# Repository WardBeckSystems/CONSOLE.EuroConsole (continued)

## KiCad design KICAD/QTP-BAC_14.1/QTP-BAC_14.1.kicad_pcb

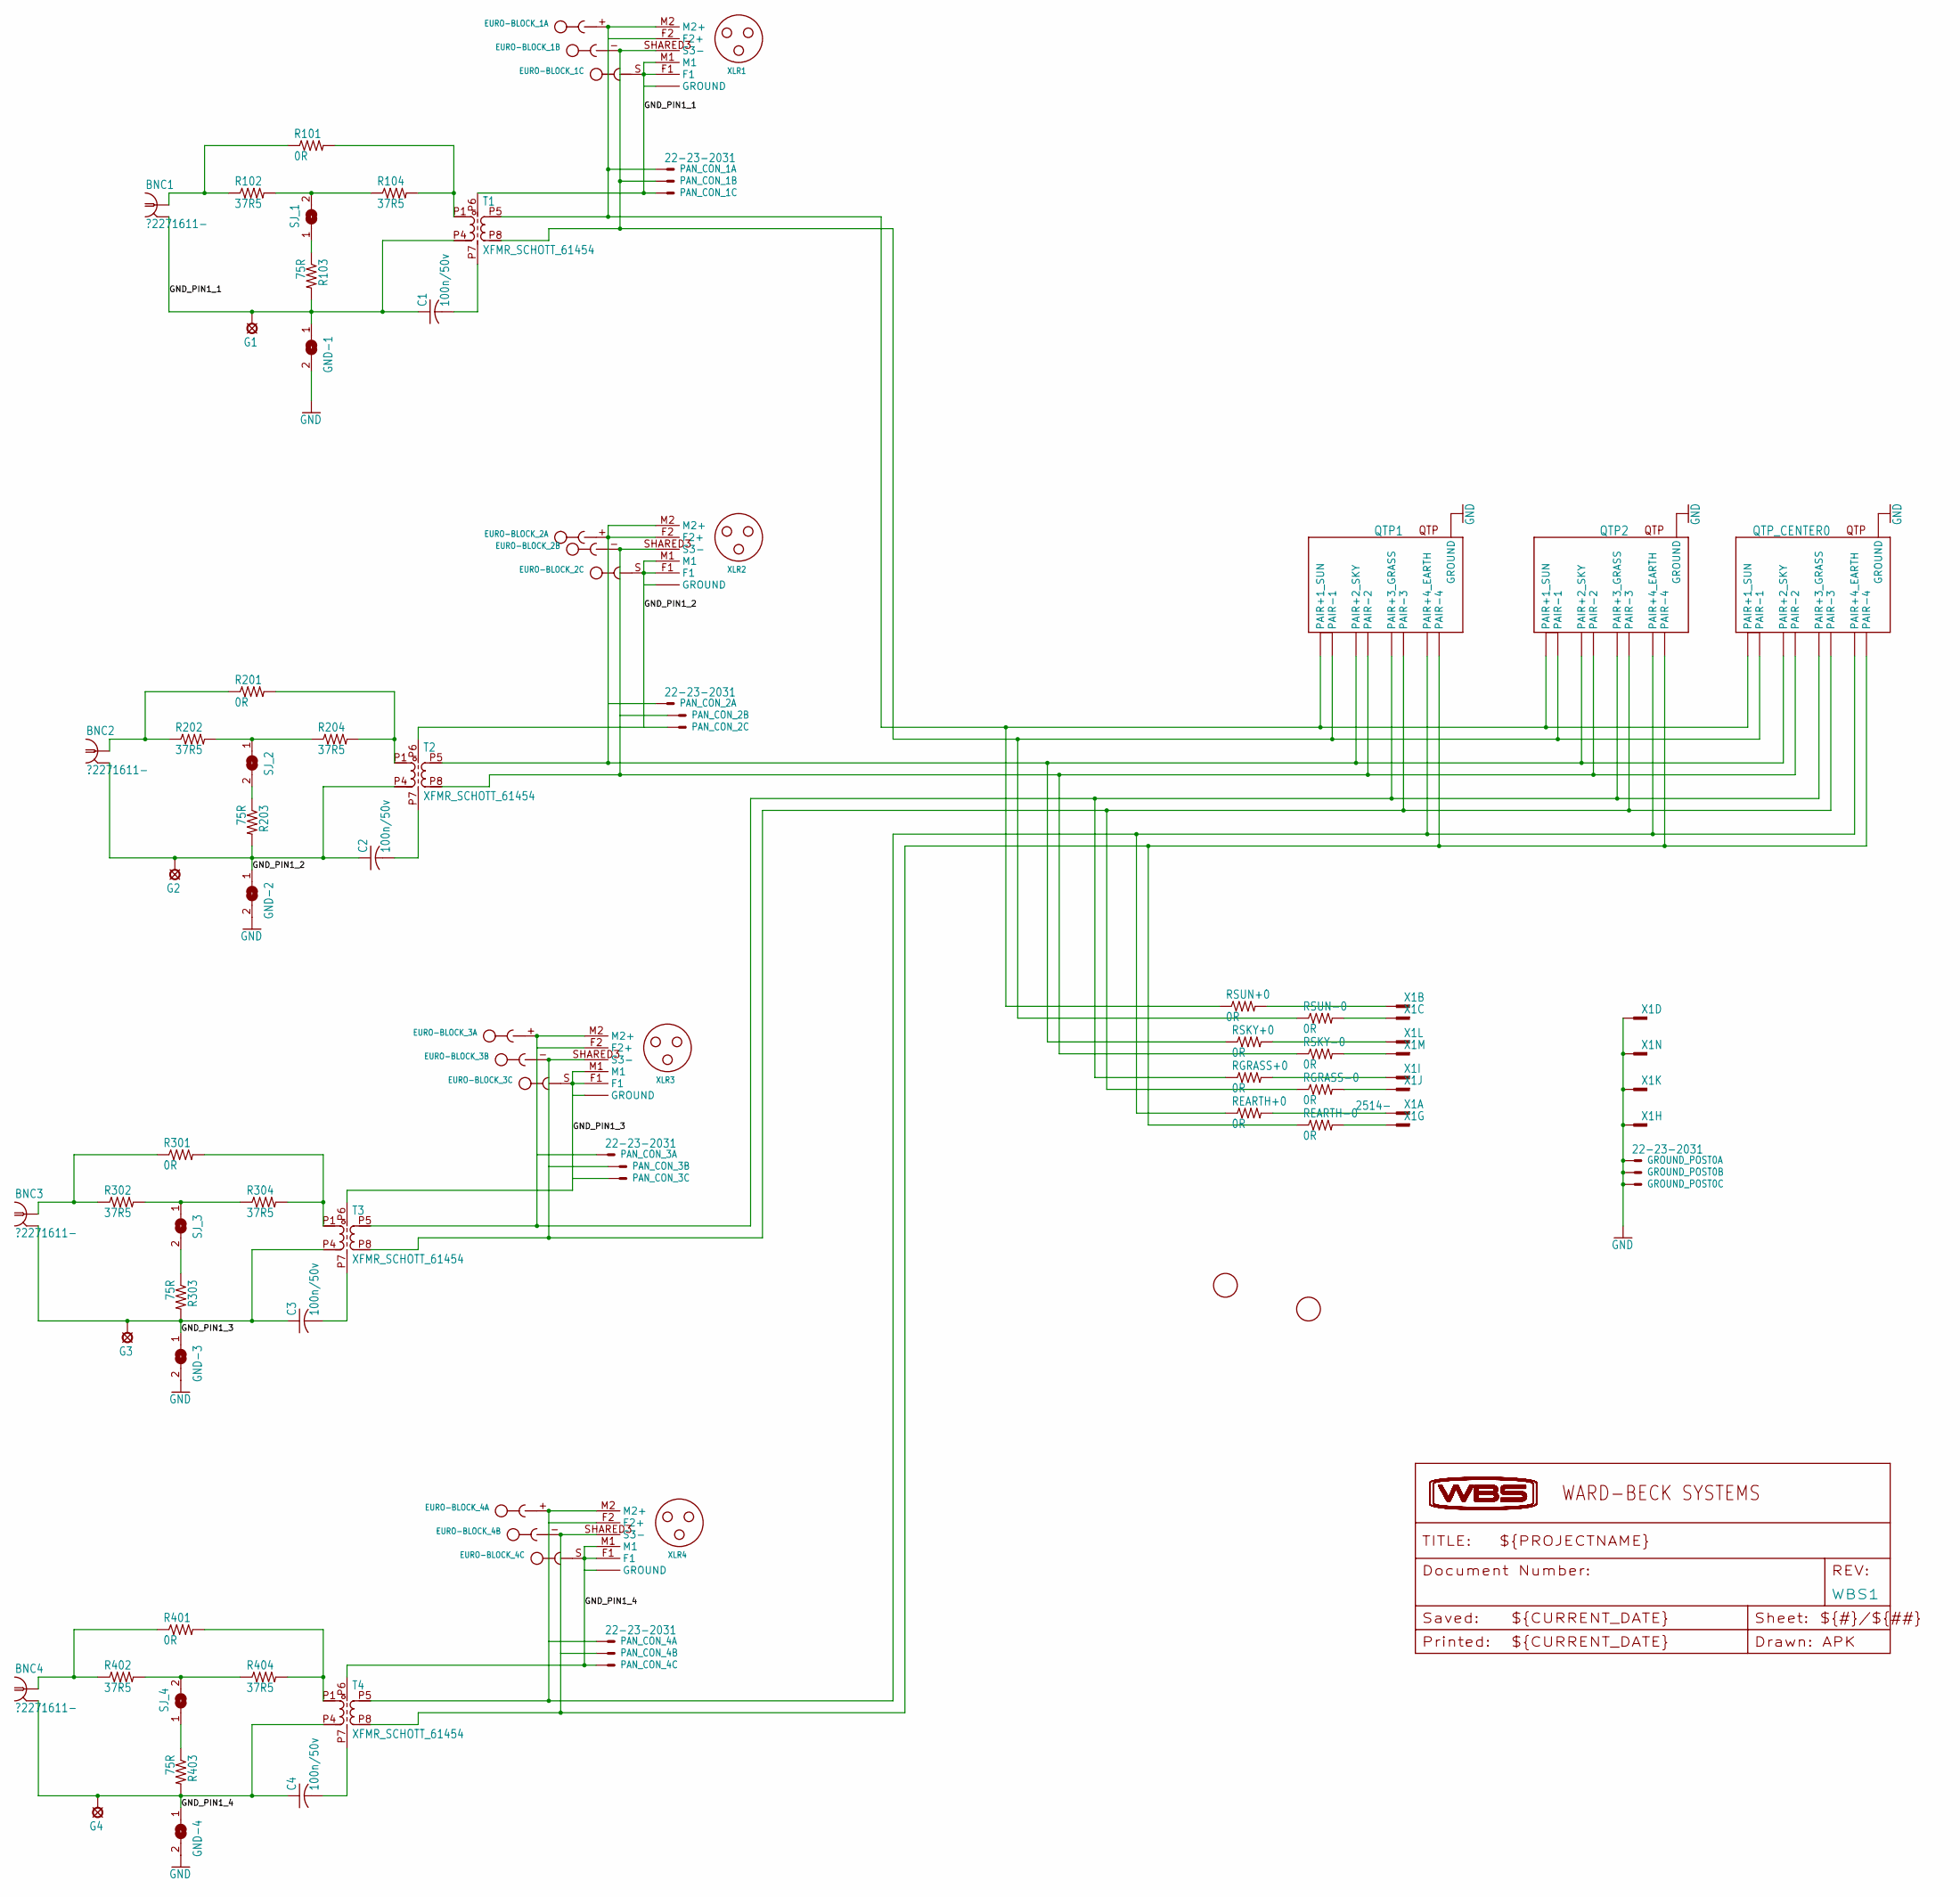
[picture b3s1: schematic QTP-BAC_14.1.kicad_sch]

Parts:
BNC1, BNC2, BNC3, BNC4: ?2271611-; AMP_227161
C1, C2, C3, C4: 100n/50v; C0805
EURO-BLOCK_1, EURO-BLOCK_2, EURO-BLOCK_3, EURO-BLOCK_4: CON-PHOENIX_RIGHT_ANGLE_3.81; CON-PHOENIX_MC1.5_3-G-3.81
G1, G2, G3, G4: LSP10
GND-1, GND-2, GND-3, GND-4: SJ
GROUND_POST0: 22-23-2031
PAN_CON_1, PAN_CON_2, PAN_CON_3, PAN_CON_4: 22-23-2031
QTP1, QTP2: CON-QTP; ASSMAN-RJ45
QTP_CENTER0: CON-QTP; ASSMAN-RJ45
R101, R201, R301, R401: 0R; R0805W
R102, R104, R202, R204, R302, R304, R402, R404: 37R5; R0805W
R103, R203, R303, R403: 75R; R0805W
REARTH+0: 0R; R0805W
REARTH-0: 0R; R0805W
RGRASS+0: 0R; R0805W
RGRASS-0: 0R; R0805W
RSKY+0: 0R; R0805W
RSKY-0: 0R; R0805W
RSUN+0: 0R; R0805W
RSUN-0: 0R; R0805W
SJ_1, SJ_2, SJ_3, SJ_4: SJ
T1, T2, T3, T4: XFMR_SCHOTT_61454; SCHOTT_61454
U$1, U$2: FIDUCIAL; FIDUCIAL_1MM
WBS1: WBS-DOCUMENT_INFO_FRAME; WBS-FRAME_PCB
X1: 2514-; PAK100_2500-14
XLR1, XLR2, XLR3, XLR4: CON-XLR-NEUTRIK_A_BISEXUAL; CON_NEUTRIK_A_BISEXUAL_H

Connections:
CH1-1: EURO-BLOCK_1.-, PAN_CON_1.2, QTP1.P1- (PAIR-1), QTP2.P1- (PAIR-1), QTP_CENTER0.P1- (PAIR-1), RSUN-0.1, T1.P8, XLR1.SHARED3 (S3-)
CH2+1: EURO-BLOCK_2.+, PAN_CON_2.1, QTP1.P2+ (PAIR+2_SKY), QTP2.P2+ (PAIR+2_SKY), QTP_CENTER0.P2+ (PAIR+2_SKY), RSKY+0.1, T2.P5, XLR2.F2 (F2+), XLR2.M2 (M2+)
CH2-1: EURO-BLOCK_2.-, PAN_CON_2.2, QTP1.P2- (PAIR-2), QTP2.P2- (PAIR-2), QTP_CENTER0.P2- (PAIR-2), RSKY-0.1, T2.P8, XLR2.SHARED3 (S3-)
CH3+1: EURO-BLOCK_3.+, PAN_CON_3.1, QTP1.P3+ (PAIR+3_GRASS), QTP2.P3+ (PAIR+3_GRASS), QTP_CENTER0.P3+ (PAIR+3_GRASS), RGRASS+0.1, T3.P5, XLR3.F2 (F2+), XLR3.M2 (M2+)
CH3-1: EURO-BLOCK_3.-, PAN_CON_3.2, QTP1.P3- (PAIR-3), QTP2.P3- (PAIR-3), QTP_CENTER0.P3- (PAIR-3), RGRASS-0.1, T3.P8, XLR3.SHARED3 (S3-)
CH4+1: EURO-BLOCK_4.+, PAN_CON_4.1, QTP1.P4+ (PAIR+4_EARTH), QTP2.P4+ (PAIR+4_EARTH), QTP_CENTER0.P4+ (PAIR+4_EARTH), REARTH+0.1, T4.P5, XLR4.F2 (F2+), XLR4.M2 (M2+)
CH4-1: EURO-BLOCK_4.-, PAN_CON_4.2, QTP1.P4- (PAIR-4), QTP2.P4- (PAIR-4), QTP_CENTER0.P4- (PAIR-4), REARTH-0.1, T4.P8, XLR4.SHARED3 (S3-)
GND: GND-1.2, GND-2.2, GND-3.2, GND-4.2, GROUND_POST0.1, GROUND_POST0.2, GROUND_POST0.3, QTP1.P$9 (GROUND), QTP1.P$10 (GROUND), QTP1.P$11 (GROUND), QTP1.P$12 (GROUND), QTP2.P$9 (GROUND), QTP2.P$10 (GROUND), QTP2.P$11 (GROUND), QTP2.P$12 (GROUND), QTP_CENTER0.P$9 (GROUND), QTP_CENTER0.P$10 (GROUND), QTP_CENTER0.P$11 (GROUND), QTP_CENTER0.P$12 (GROUND), X1.3, X1.6, X1.9, X1.12
GND_PIN1_2: BNC2.2, C2.1, EURO-BLOCK_2.S, G2.MP, GND-2.1, PAN_CON_2.3, R203.2, T2.P4, T2.P6, XLR2.CHASSIS (GROUND), XLR2.F1, XLR2.GROUND, XLR2.M1
GND_PIN1_3: BNC3.2, C3.1, EURO-BLOCK_3.S, G3.MP, GND-3.1, PAN_CON_3.3, R303.2, T3.P4, T3.P6, XLR3.CHASSIS (GROUND), XLR3.F1, XLR3.GROUND, XLR3.M1
GND_PIN1_4: BNC4.2, C4.1, EURO-BLOCK_4.S, G4.MP, GND-4.1, PAN_CON_4.3, R403.2, T4.P4, T4.P6, XLR4.CHASSIS (GROUND), XLR4.F1, XLR4.GROUND, XLR4.M1
unnamed: R102.2, R104.1, SJ_1.2
unnamed: C1.2, T1.P7
unnamed: R101.2, R104.2, T1.P1
unnamed: R103.1, SJ_1.1
unnamed: BNC1.1, R101.1, R102.1
unnamed: R203.1, SJ_2.2
unnamed: R303.1, SJ_3.2
unnamed: R201.2, R204.2, T2.P1
unnamed: R202.2, R204.1, SJ_2.1
unnamed: BNC2.1, R201.1, R202.1
unnamed: C2.2, T2.P7
unnamed: R403.1, SJ_4.1
unnamed: R301.2, R304.2, T3.P1
unnamed: R302.2, R304.1, SJ_3.1
unnamed: BNC3.1, R301.1, R302.1
unnamed: C3.2, T3.P7
unnamed: R401.2, R404.2, T4.P1
unnamed: R402.2, R404.1, SJ_4.2
unnamed: BNC4.1, R401.1, R402.1
unnamed: C4.2, T4.P7
unnamed: REARTH-0.2, X1.2
unnamed: REARTH+0.2, X1.1
unnamed: RGRASS-0.2, X1.5
unnamed: RSUN+0.2, X1.10
unnamed: RGRASS+0.2, X1.4
unnamed: RSKY-0.2, X1.8
unnamed: RSKY+0.2, X1.7
unnamed: RSUN-0.2, X1.11

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
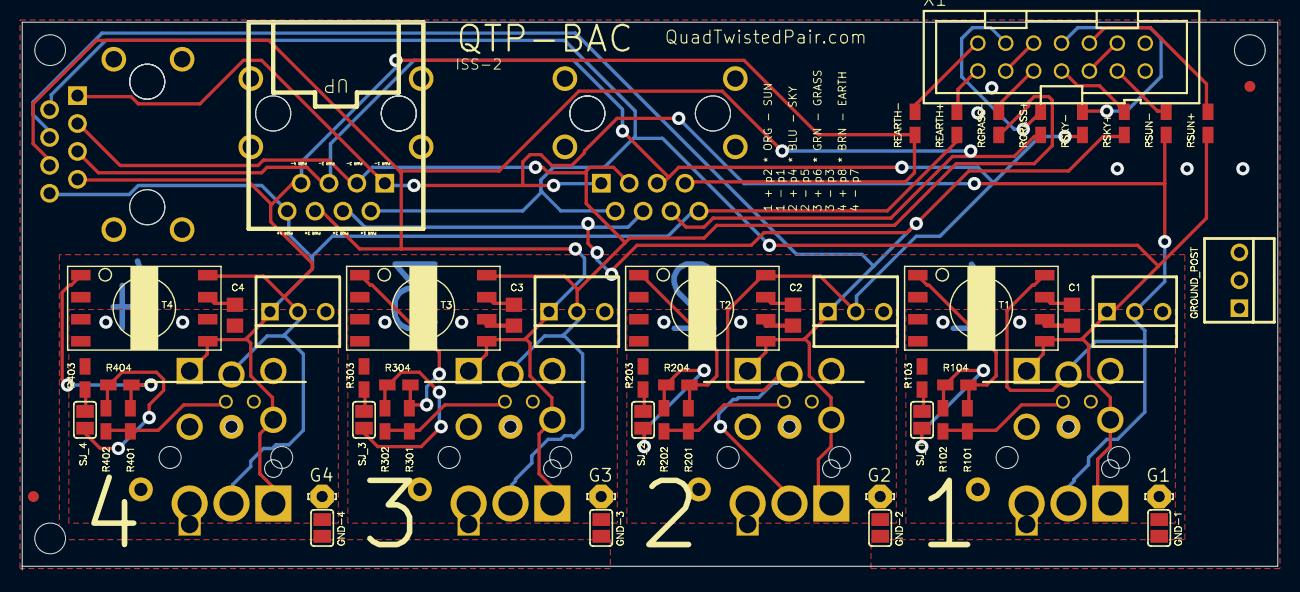
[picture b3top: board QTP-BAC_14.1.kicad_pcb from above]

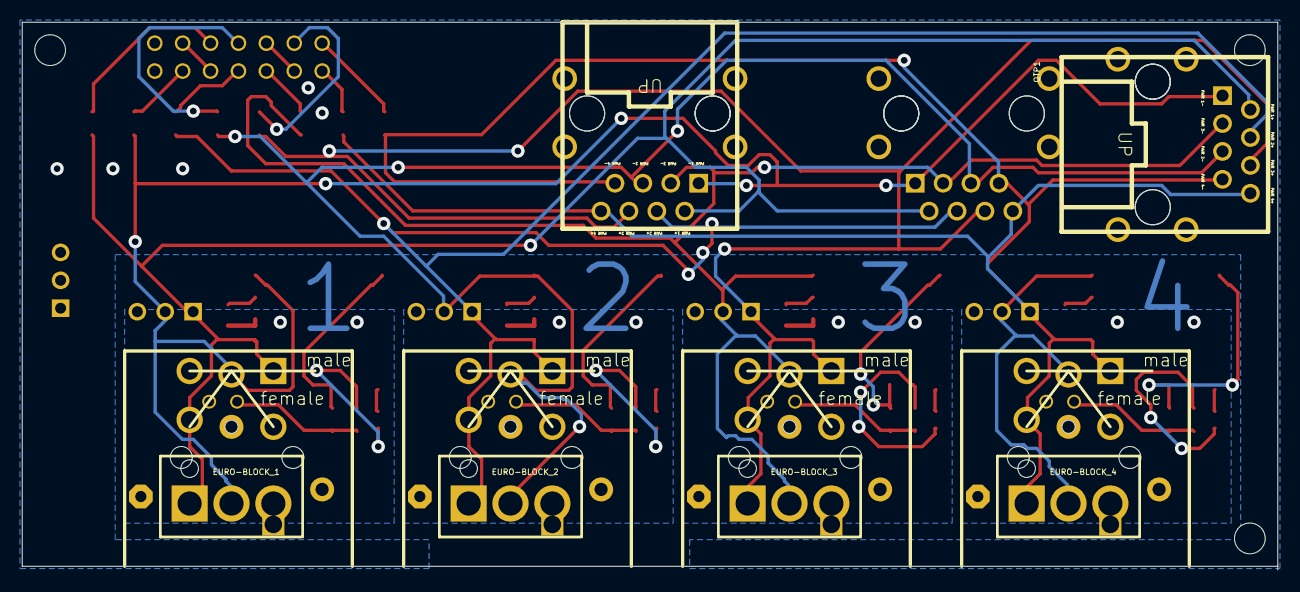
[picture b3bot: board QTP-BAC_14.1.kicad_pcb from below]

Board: 2 copper layers, 114.3 x 49.5 mm, 112 parts (6 on the bottom side), 41 nets.

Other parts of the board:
U$4: C1-4-150731-094535
U$5: C2-5-150731-094535
U$6: C3-6-150731-094535
U$7: C4-7-150731-094535
U$9: GND_1-8-150731-094535
U$10: GND_2-9-150731-094535
U$11: GND_3-10-150731-094535
U$12: GND_4-11-150731-094535
U$13: GROUND_P-12-150731-094535
U$18: R101-17-150731-094535
U$19: R102-18-150731-094535
U$20: R103-19-150731-094535
U$21: R104-20-150731-094535
U$22: R201-21-150731-094535
U$23: R202-22-150731-094535
U$24: R203-23-150731-094535
U$25: R204-24-150731-094535
U$26: R301-25-150731-094535
U$27: R302-26-150731-094535
U$28: R303-27-150731-094535
U$29: R304-28-150731-094535
U$30: R401-29-150731-094535
U$31: R402-30-150731-094535
U$32: R403-31-150731-094535
U$33: R404-32-150731-094535
U$34: REARTH_-33-150731-094535
U$35: REARTH_-34-150731-094535
U$36: RGRASS_-35-150731-094535
U$37: RGRASS_-36-150731-094535
U$38: RSKY_-37-150731-094535
U$39: RSKY_-38-150731-094535
U$40: RSUN_-39-150731-094535
U$41: RSUN_-40-150731-094535
U$42: SJ_1-41-150731-094535
U$43: SJ_2-42-150731-094536
U$44: SJ_3-43-150731-094536
U$45: SJ_4-44-150731-094536
U$46: GND_PIN1_1; T1-45-150731-094536
U$47: GND_PIN1_2; T2-46-150731-094536
U$48: gnd; T3-47-150731-094536
U$49: gnd; T4-48-150731-094536
UNK_HOLE_0: dummyfp0
UNK_HOLE_1: dummyfp1
UNK_HOLE_2: dummyfp2

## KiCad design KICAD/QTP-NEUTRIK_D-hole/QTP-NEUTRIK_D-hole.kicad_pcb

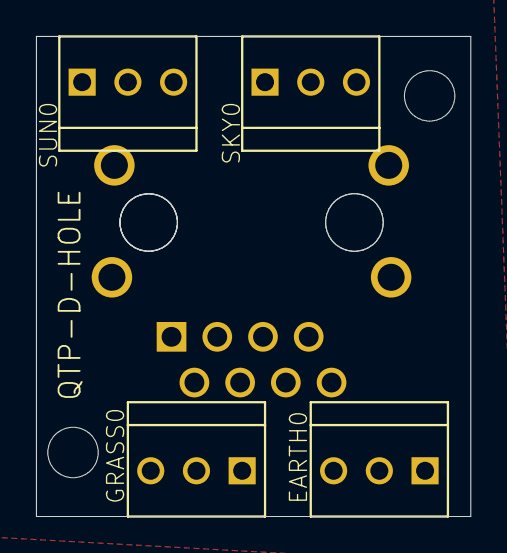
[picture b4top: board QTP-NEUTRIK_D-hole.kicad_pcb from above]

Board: 2 copper layers, 24.1 x 26.7 mm, 7 parts (1 on the bottom side), 9 nets, no tracks yet.

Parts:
EARTH0: CON-WBS-LOCKING-0.1-3
GRASS0: CON-WBS-LOCKING-0.1-3
SKY0: CON-WBS-LOCKING-0.1-3
SUN0: CON-WBS-LOCKING-0.1-3
U$1: CON-QTP_VERT; ASSMAN-RJ45_VERT
UNK_HOLE_0: dummyfp0
UNK_HOLE_1: dummyfp1

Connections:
GND: EARTH0.P$3, GRASS0.P$3, SKY0.P$3, SUN0.P$3, U$1.P$9, U$1.P$10, U$1.P$11, U$1.P$12
unnamed: SUN0.P$1, U$1.P$2
unnamed: SUN0.P$2, U$1.P$1
unnamed: SKY0.P$1, U$1.P$4
unnamed: GRASS0.P$1, U$1.P$6
unnamed: GRASS0.P$2, U$1.P$3
unnamed: EARTH0.P$1, U$1.P$8
unnamed: EARTH0.P$2, U$1.P$7
SUN_N: SKY0.P$2, U$1.P$5

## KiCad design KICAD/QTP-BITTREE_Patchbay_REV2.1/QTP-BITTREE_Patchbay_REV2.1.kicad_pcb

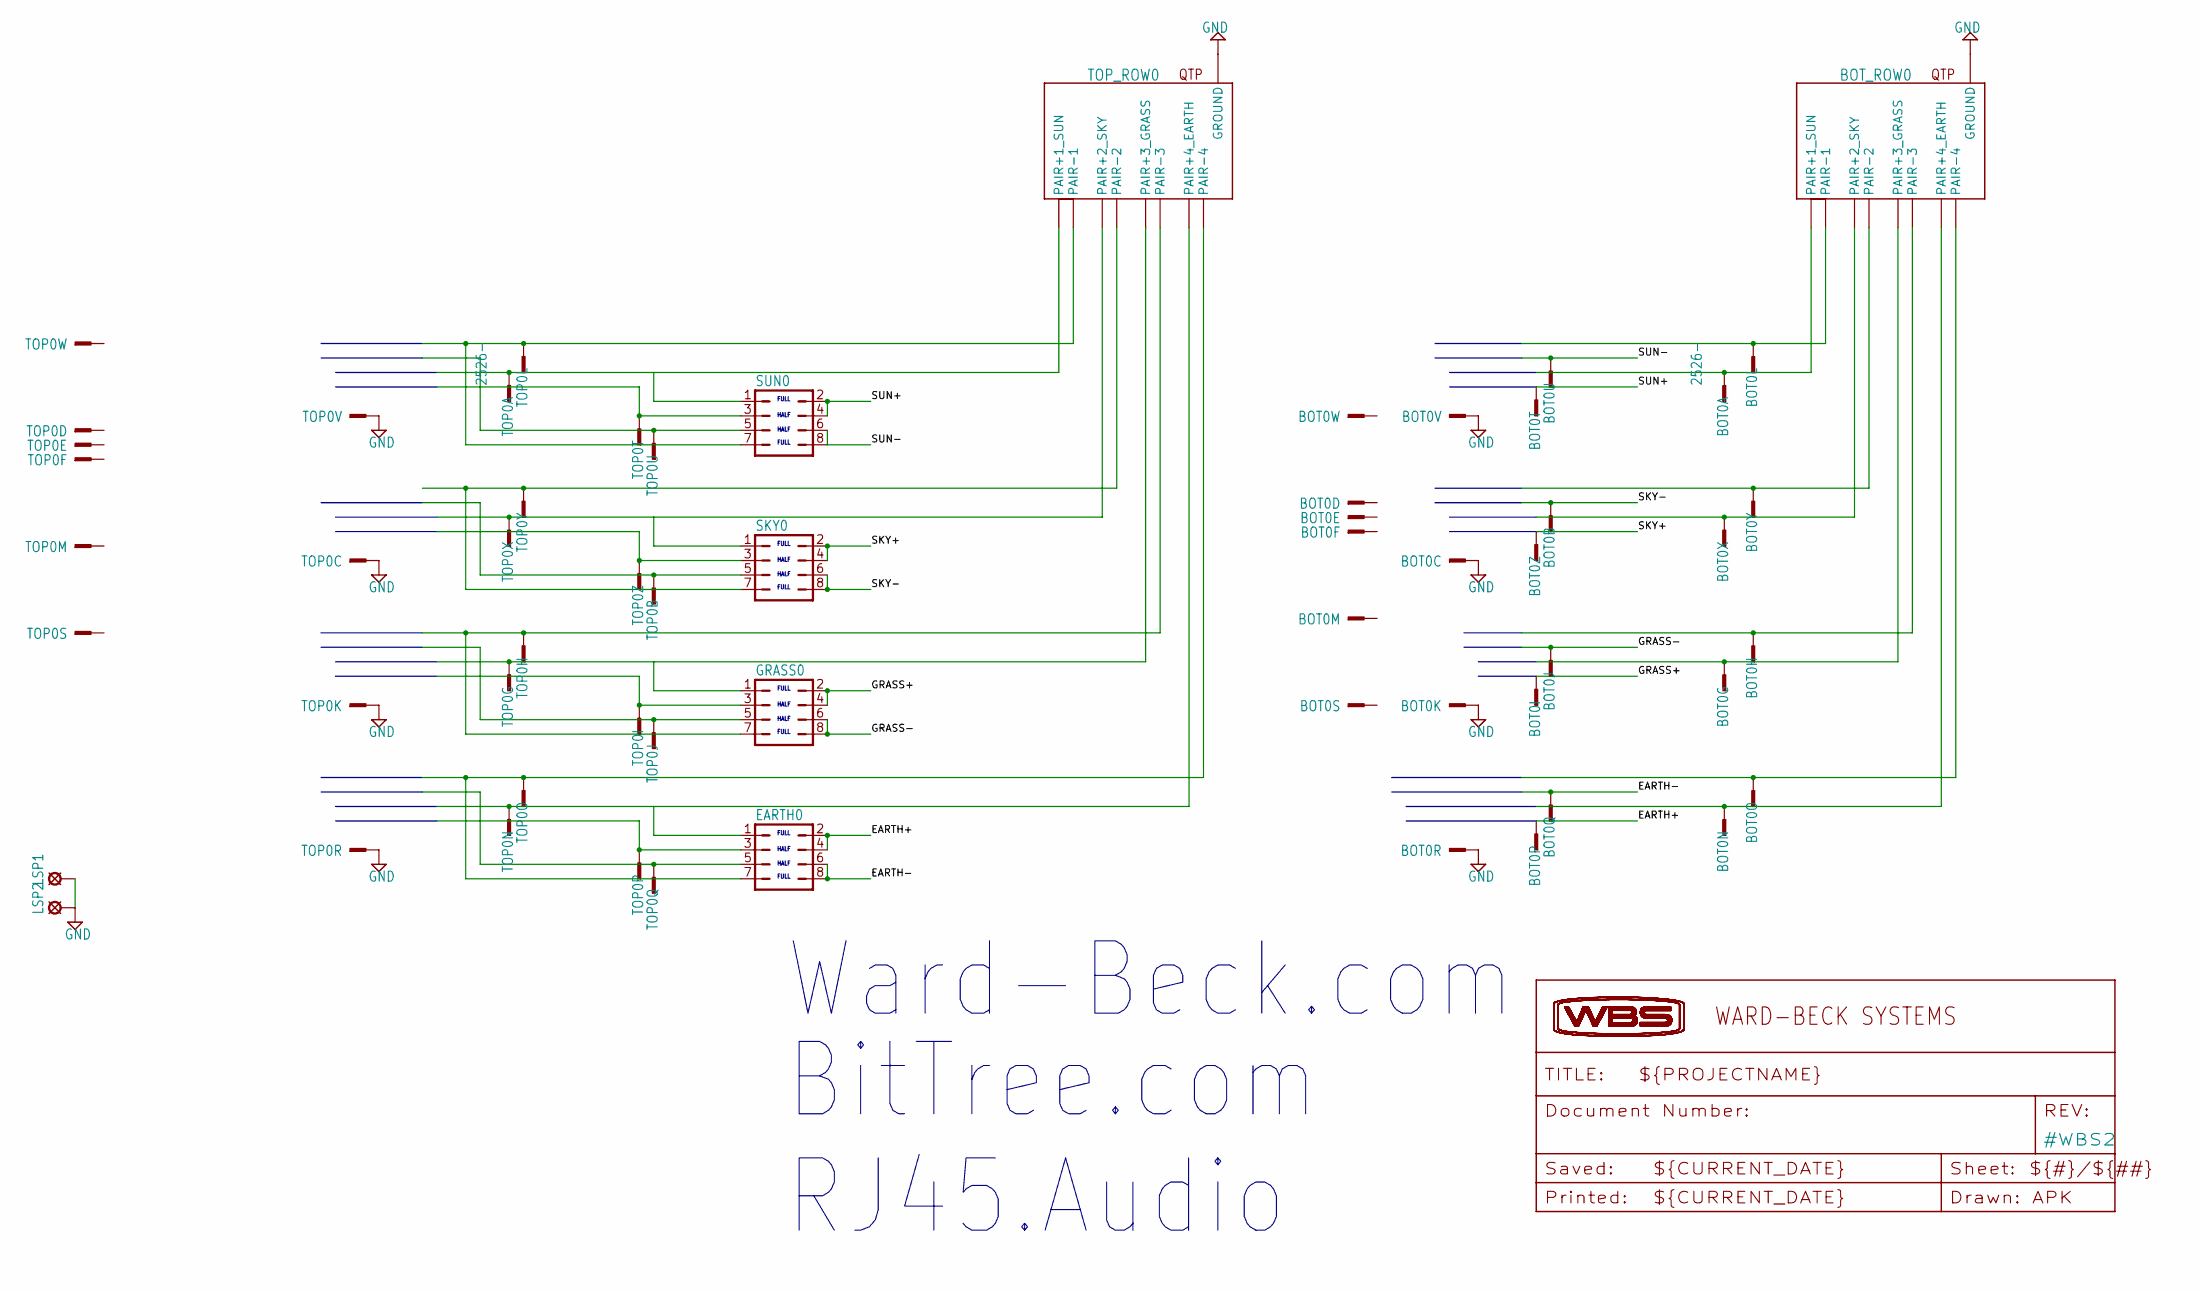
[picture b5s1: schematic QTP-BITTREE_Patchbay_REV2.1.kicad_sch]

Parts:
BOT0: 2526-; PAK100_2500-26
BOT_ROW0: CON-QTP_VERT; ASSMAN-RJ45_VERT
EARTH0: JP4Q
GRASS0: JP4Q
LSP1, LSP2: LSP13
SKY0: JP4Q
SUN0: JP4Q
TOP0: 2526-; PAK100_2500-26
TOP_ROW0: CON-QTP_VERT; ASSMAN-RJ45_VERT

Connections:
EARTH+: BOT0.23, EARTH0.2, EARTH0.4
EARTH-: BOT0.24, EARTH0.6, EARTH0.8
GND: BOT0.5, BOT0.11, BOT0.19, BOT0.25, BOT_ROW0.P$9 (GROUND), BOT_ROW0.P$10 (GROUND), BOT_ROW0.P$11 (GROUND), BOT_ROW0.P$12 (GROUND), LSP1.MP, LSP2.MP, TOP0.5, TOP0.11, TOP0.19, TOP0.25, TOP_ROW0.P$9 (GROUND), TOP_ROW0.P$10 (GROUND), TOP_ROW0.P$11 (GROUND), TOP_ROW0.P$12 (GROUND)
GRASS+: BOT0.17, GRASS0.2, GRASS0.4
GRASS-: BOT0.18, GRASS0.6, GRASS0.8
unnamed: SUN0.7, TOP0.2, TOP_ROW0.P$1 (PAIR-1)
unnamed: SKY0.1, TOP0.7, TOP_ROW0.P$4 (PAIR+2_SKY)
unnamed: BOT0.1, BOT_ROW0.P$2 (PAIR+1_SUN)
unnamed: GRASS0.1, TOP0.15, TOP_ROW0.P$6 (PAIR+3_GRASS)
unnamed: BOT0.2, BOT_ROW0.P$1 (PAIR-1)
unnamed: EARTH0.1, TOP0.21, TOP_ROW0.P$8 (PAIR+4_EARTH)
unnamed: SUN0.3, TOP0.3
unnamed: SUN0.5, TOP0.4
unnamed: BOT0.7, BOT_ROW0.P$4 (PAIR+2_SKY)
unnamed: SKY0.7, TOP0.8, TOP_ROW0.P$5 (PAIR-2)
unnamed: SKY0.3, TOP0.9
unnamed: SKY0.5, TOP0.10
unnamed: BOT0.15, BOT_ROW0.P$6 (PAIR+3_GRASS)
unnamed: GRASS0.7, TOP0.16, TOP_ROW0.P$3 (PAIR-3)
unnamed: GRASS0.3, TOP0.17
unnamed: GRASS0.5, TOP0.18
unnamed: BOT0.21, BOT_ROW0.P$8 (PAIR+4_EARTH)
unnamed: EARTH0.7, TOP0.22, TOP_ROW0.P$7 (PAIR-4)
unnamed: EARTH0.3, TOP0.23
unnamed: EARTH0.5, TOP0.24
unnamed: BOT0.8, BOT_ROW0.P$5 (PAIR-2)
unnamed: BOT0.16, BOT_ROW0.P$3 (PAIR-3)
unnamed: BOT0.22, BOT_ROW0.P$7 (PAIR-4)
SKY+: BOT0.9, SKY0.2, SKY0.4
SKY-: BOT0.10, SKY0.6, SKY0.8
SUN+: BOT0.3, SUN0.2, SUN0.4
SUN-: BOT0.4, SUN0.6, SUN0.8
TOP-P1: SUN0.1, TOP0.1, TOP_ROW0.P$2 (PAIR+1_SUN)

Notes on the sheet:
HALF
FULL
Ward-Beck.com
BitTree.com RJ45.Audio

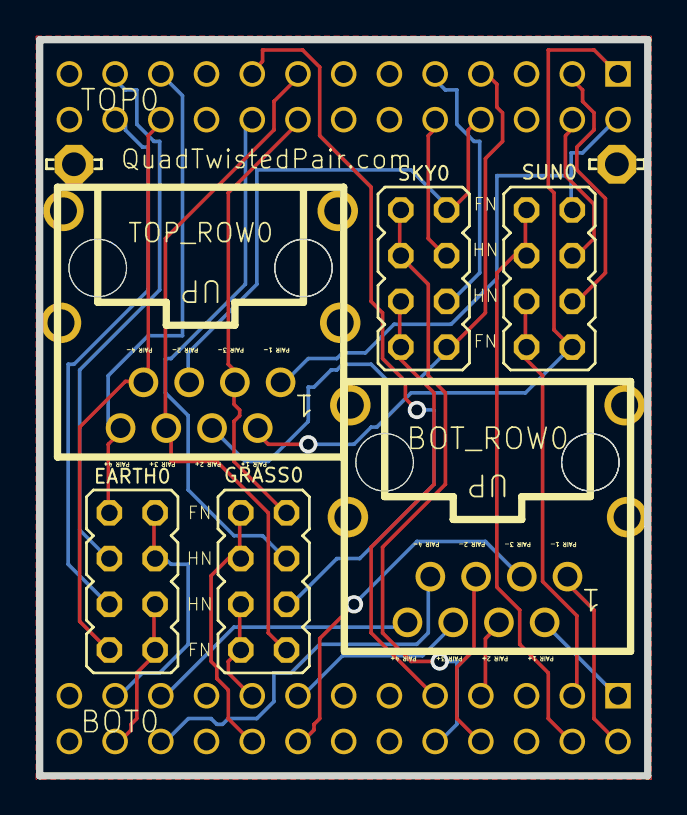
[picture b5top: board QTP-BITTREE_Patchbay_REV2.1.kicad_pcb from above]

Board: 2 copper layers, 33.8 x 40.9 mm, 10 parts (0 on the bottom side), 33 nets.

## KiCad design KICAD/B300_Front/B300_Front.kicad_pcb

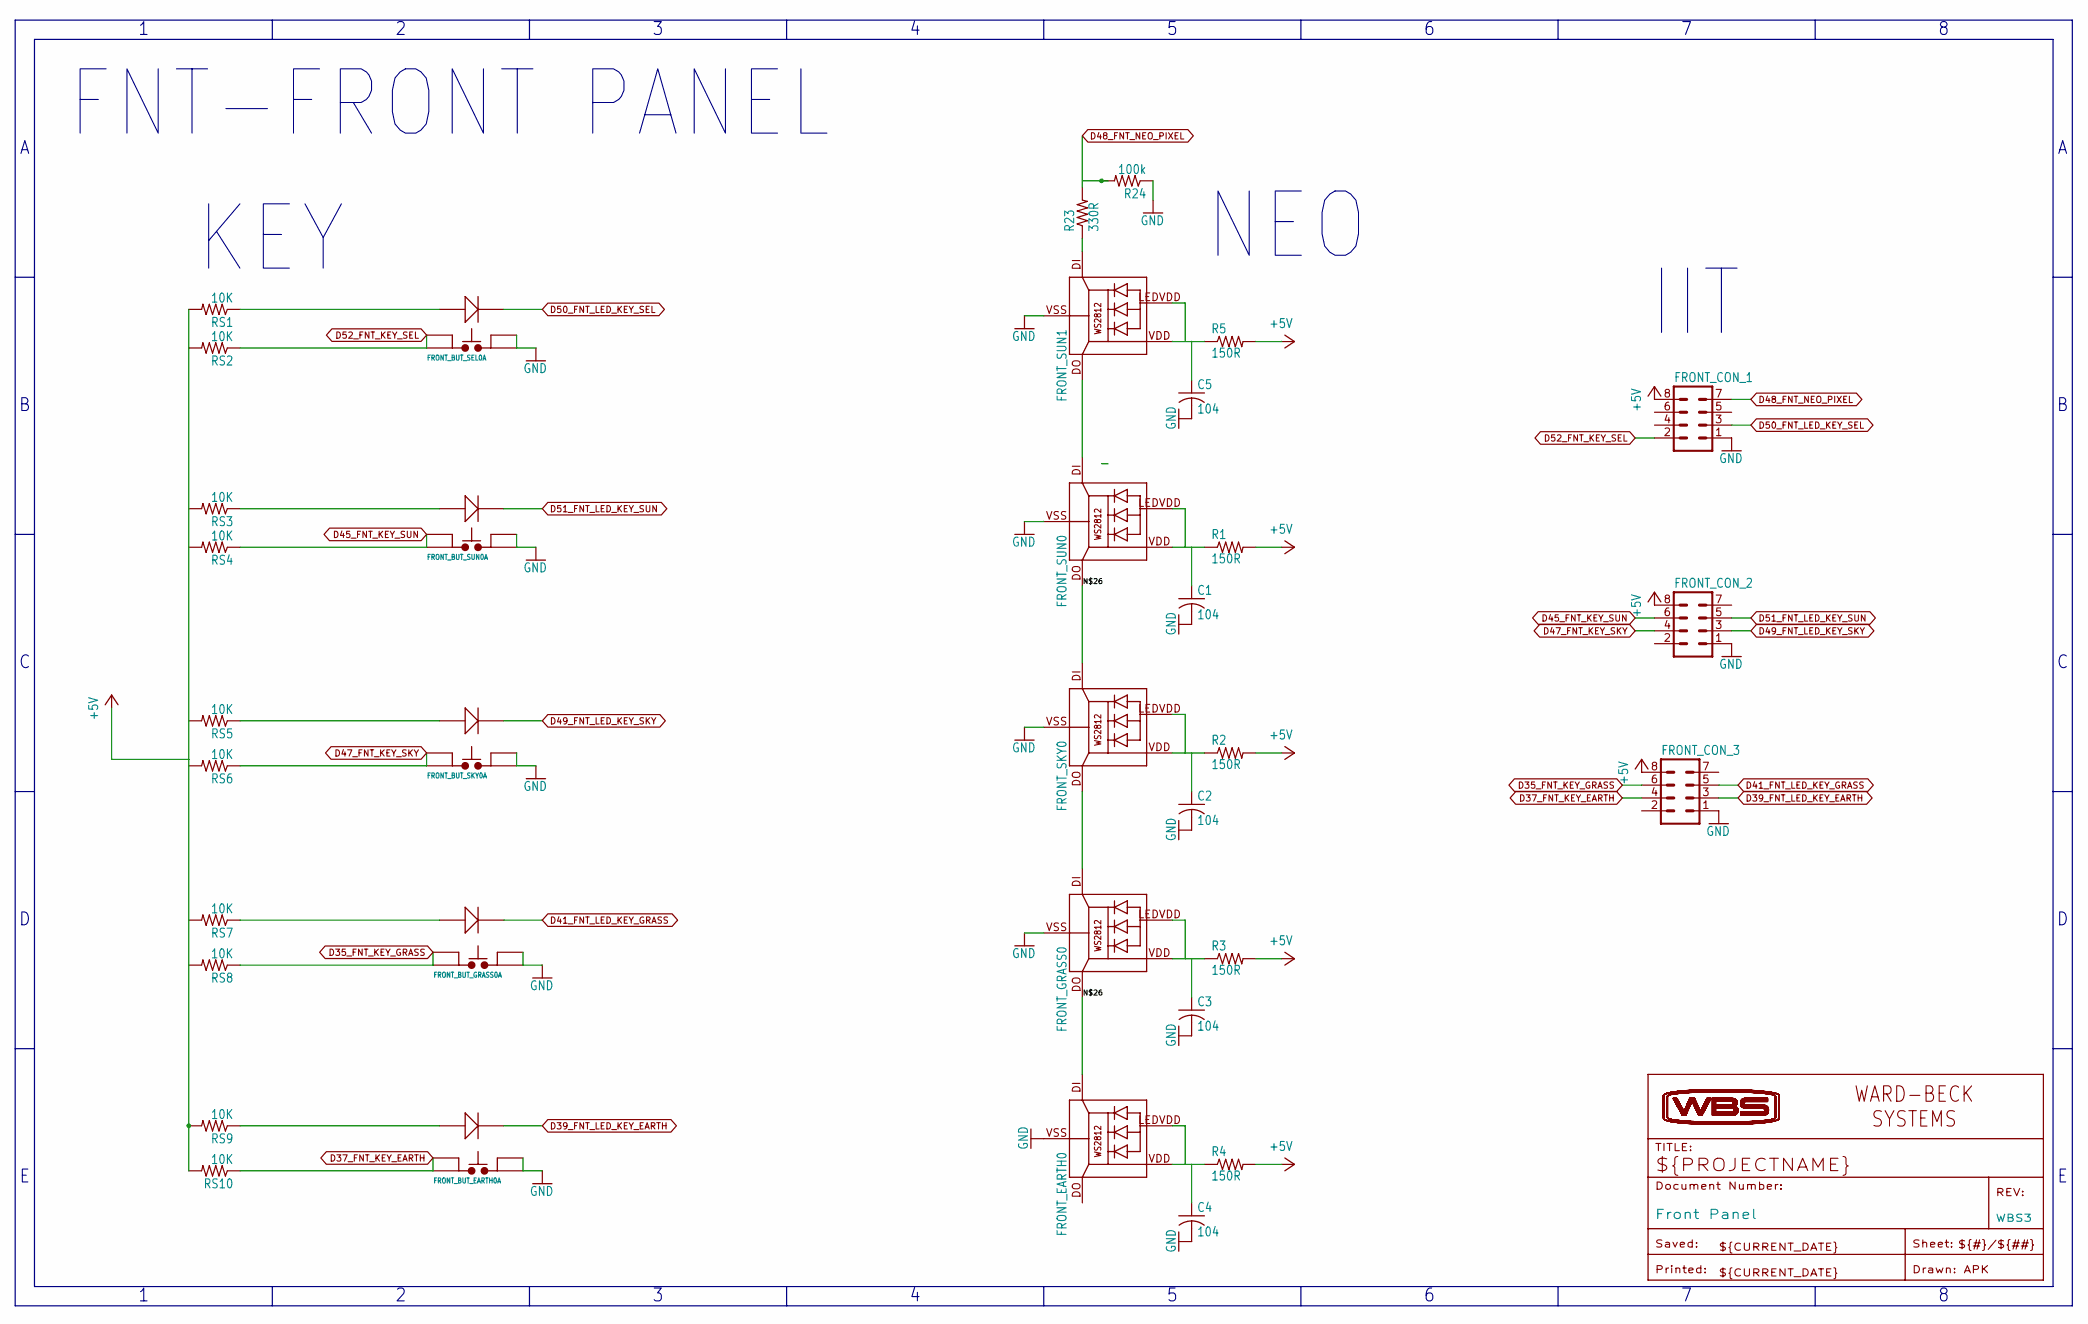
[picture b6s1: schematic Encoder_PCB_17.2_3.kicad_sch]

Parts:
C1, C2, C3, C4, C5: 104; C0805
FRONT_BUT_EARTH0: SWITCH-POD-BUTTON_WITH_LED; SWITCH-PODBUTTON
FRONT_BUT_GRASS0: SWITCH-POD-BUTTON_WITH_LED; SWITCH-PODBUTTON
FRONT_BUT_SEL0: SWITCH-POD-BUTTON_WITH_LED; SWITCH-PODBUTTON
FRONT_BUT_SKY0: SWITCH-POD-BUTTON_WITH_LED; SWITCH-PODBUTTON
FRONT_BUT_SUN0: SWITCH-POD-BUTTON_WITH_LED; SWITCH-PODBUTTON
FRONT_CON_1, FRONT_CON_2, FRONT_CON_3: MA04-2
FRONT_EARTH0: WS2812
FRONT_GRASS0: WS2812
FRONT_SKY0: WS2812
FRONT_SUN0, FRONT_SUN1: WS2812
R1, R2, R3, R4, R5: 150R; M0805
R23: 330R; M0805
R24: 100k; M0805
RS1, RS2, RS3, RS4, RS5, RS6, RS7, RS8, RS9, RS10: 10K; M0805
WBS3: Front Panel; WBS-FRAME_PCB

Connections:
+5V: FRONT_CON_1.8, FRONT_CON_2.8, FRONT_CON_3.8, R1.2, R2.2, R3.2, R4.2, R5.2, RS1.2, RS2.2, RS3.2, RS4.2, RS5.2, RS6.2, RS7.2, RS8.2, RS9.2, RS10.2
D35_FNT_KEY_GRASS: FRONT_BUT_GRASS0.SW1A, FRONT_BUT_GRASS0.SW2A, FRONT_CON_3.6, RS8.1
D37_FNT_KEY_EARTH: FRONT_BUT_EARTH0.SW1A, FRONT_BUT_EARTH0.SW2A, FRONT_CON_3.4, RS10.1
D39_FNT_LED_KEY_EARTH: FRONT_BUT_EARTH0.LEDB, FRONT_CON_3.3
D41_FNT_LED_KEY_GRASS: FRONT_BUT_GRASS0.LEDB, FRONT_CON_3.5
D45_FNT_KEY_SUN: FRONT_BUT_SUN0.SW1A, FRONT_BUT_SUN0.SW2A, FRONT_CON_2.6, RS4.1
D47_FNT_KEY_SKY: FRONT_BUT_SKY0.SW1A, FRONT_BUT_SKY0.SW2A, FRONT_CON_2.4, RS6.1
D48_FNT_NEO_PIXEL: FRONT_CON_1.7, R23.2, R24.2
D49_FNT_LED_KEY_SKY: FRONT_BUT_SKY0.LEDB, FRONT_CON_2.3
D50_FNT_LED_KEY_SEL: FRONT_BUT_SEL0.LEDB, FRONT_CON_1.3
D51_FNT_LED_KEY_SUN: FRONT_BUT_SUN0.LEDB, FRONT_CON_2.5
D52_FNT_KEY_SEL: FRONT_BUT_SEL0.SW1A, FRONT_BUT_SEL0.SW2A, FRONT_CON_1.2, RS2.1
GND: C1.2, C2.2, C3.2, C4.2, C5.2, FRONT_BUT_EARTH0.SW1B, FRONT_BUT_EARTH0.SW2B, FRONT_BUT_GRASS0.SW1B, FRONT_BUT_GRASS0.SW2B, FRONT_BUT_SEL0.SW1B, FRONT_BUT_SEL0.SW2B, FRONT_BUT_SKY0.SW1B, FRONT_BUT_SKY0.SW2B, FRONT_BUT_SUN0.SW1B, FRONT_BUT_SUN0.SW2B, FRONT_CON_1.1, FRONT_CON_2.1, FRONT_CON_3.1, FRONT_EARTH0.VSS (GND), FRONT_GRASS0.VSS (GND), FRONT_SKY0.VSS (GND), FRONT_SUN0.VSS (GND), FRONT_SUN1.VSS (GND), R24.1
unnamed: FRONT_BUT_GRASS0.LEDA, RS7.1
unnamed: FRONT_BUT_SKY0.LEDA, RS5.1
unnamed: C1.1, FRONT_SUN0.LEDVDD, FRONT_SUN0.VDD, R1.1
unnamed: FRONT_BUT_SUN0.LEDA, RS3.1
unnamed: FRONT_BUT_SEL0.LEDA, RS1.1
unnamed: FRONT_GRASS0.DI, FRONT_SKY0.DO
unnamed: C2.1, FRONT_SKY0.LEDVDD, FRONT_SKY0.VDD, R2.1
unnamed: FRONT_BUT_EARTH0.LEDA, RS9.1
unnamed: C3.1, FRONT_GRASS0.LEDVDD, FRONT_GRASS0.VDD, R3.1
unnamed: FRONT_SUN0.DI, FRONT_SUN1.DO
unnamed: C4.1, FRONT_EARTH0.LEDVDD, FRONT_EARTH0.VDD, R4.1
unnamed: C5.1, FRONT_SUN1.LEDVDD, FRONT_SUN1.VDD, R5.1
unnamed: FRONT_EARTH0.DI, FRONT_GRASS0.DO, FRONT_SKY0.DI, FRONT_SUN0.DO
unnamed: FRONT_SUN1.DI, R23.1

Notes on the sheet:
FNT-FRONT PANEL
IIT
NEO
KEY

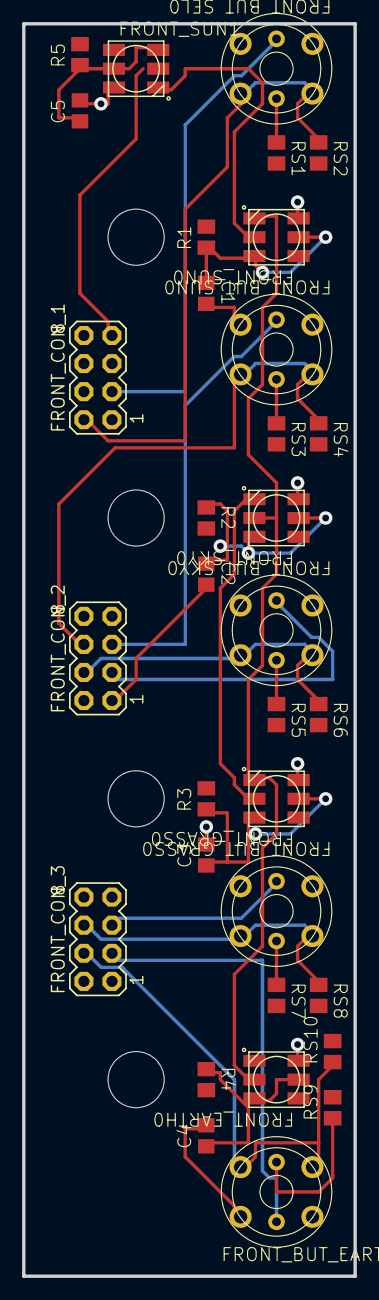
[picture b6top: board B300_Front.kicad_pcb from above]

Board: 2 copper layers, 30.0 x 113.3 mm, 37 parts (0 on the bottom side), 25 nets.

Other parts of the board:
UNK_HOLE_0: dummyfp0
UNK_HOLE_1: dummyfp1
UNK_HOLE_2: dummyfp2
UNK_HOLE_3: dummyfp3
